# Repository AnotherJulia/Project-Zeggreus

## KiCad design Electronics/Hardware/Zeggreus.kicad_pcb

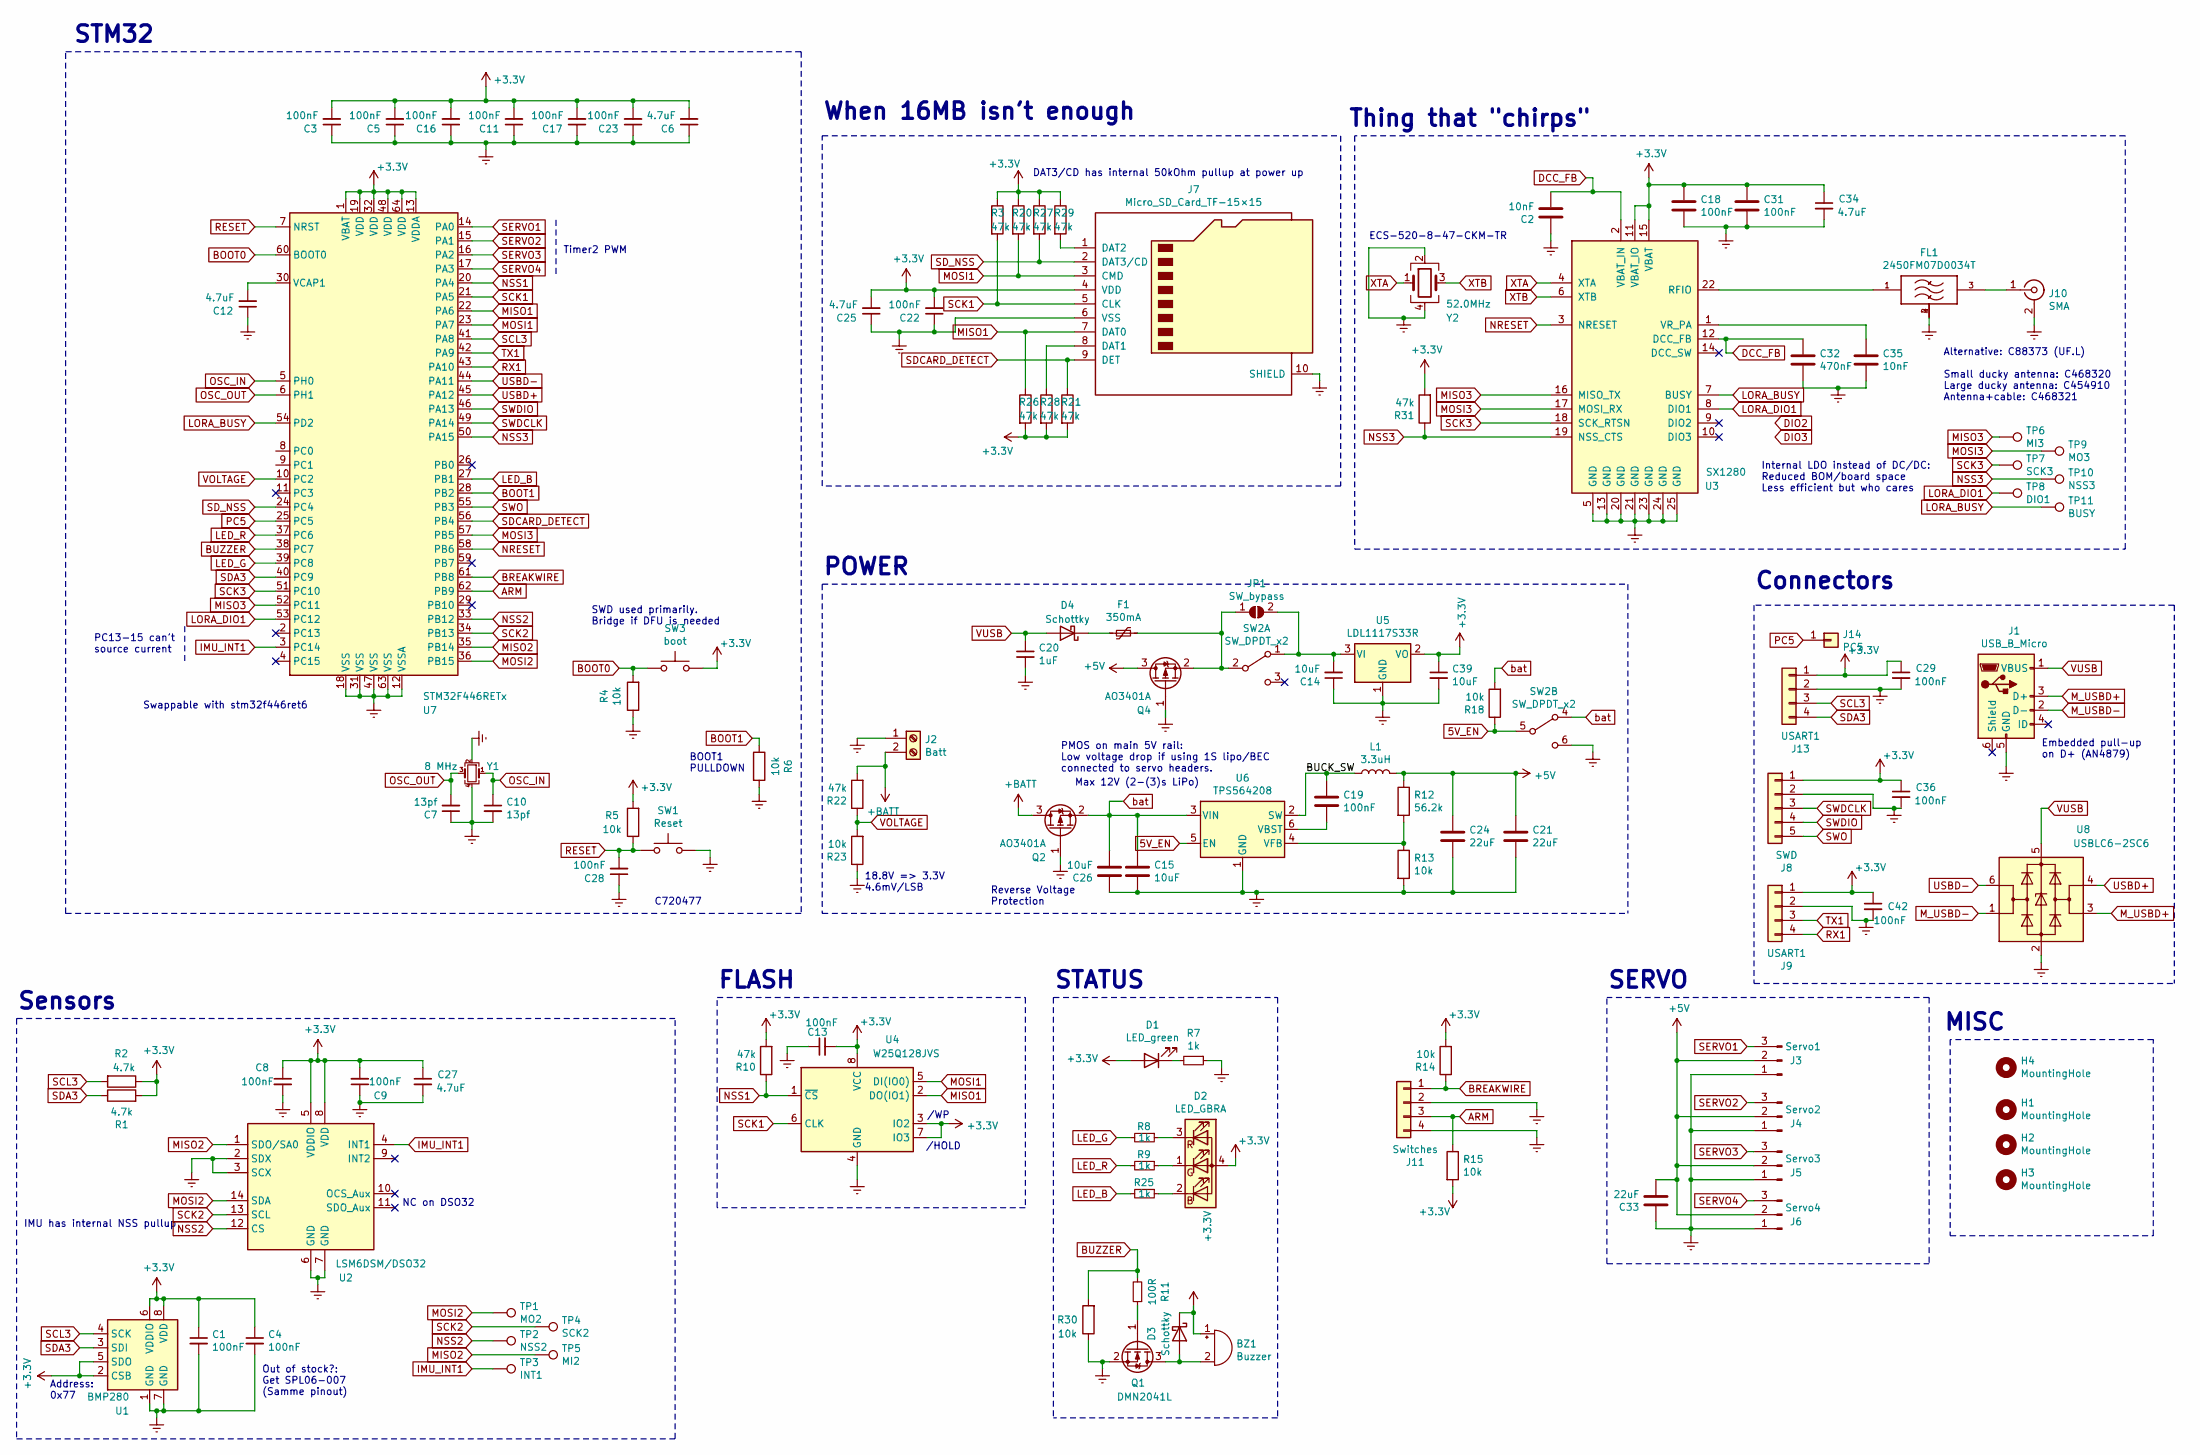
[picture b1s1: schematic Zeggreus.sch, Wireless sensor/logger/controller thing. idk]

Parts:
BZ1: Buzzer; 5x5mm_buzzer; LCSC C391030
C1, C3, C4, C5, C8, C9, C11, C13, C16, C17, C18, C19, C22, C23, C28, C29, C31, C36, C42: 100nF; C_0603_1608Metric; LCSC C45000
C2, C35: 10nF; C_0402_1005Metric; LCSC C77013
C6, C12, C25, C27, C34: 4.7uF; C_0603_1608Metric; LCSC C1705
C7, C10: 13pf; C_0603_1608Metric; LCSC C34243
C14, C15, C26, C39: 10uF; C_0805_2012Metric; LCSC C84416
C20: 1uF; C_0603_1608Metric; LCSC C26413
C21, C24, C33: 22uF; C_0805_2012Metric; LCSC C503482
C32: 470nF; C_0603_1608Metric; LCSC C106850
D1: LED_green; LED_0603_1608Metric; LCSC C205445
D2: LED_GBRA; LED_RGB_3.2X2.7mm; LCSC C375572
D3, D4: Schottky; D_SOD-123F; LCSC C353500
F1: 350mA; Fuse_1206_3216Metric; LCSC C269114
FL1: 2450FM07D0034T; FIL_2450FM07D0034T; PARTREV 1.2
H1, H2, H3, H4: MountingHole; MountingHole_3.2mm_M3
J1: USB_B_Micro; USB_Micro_B-Generic_SMT; LCSC C404968
J2: Batt; TerminalBlock_4Ucon_1x02_P3.50mm_Horizontal_blue; LCSC C474892
J3: Servo1; PinHeader_1x03_P2.54mm_Vertical
J4: Servo2; PinHeader_1x03_P2.54mm_Vertical
J5: Servo3; PinHeader_1x03_P2.54mm_Vertical
J6: Servo4; PinHeader_1x03_P2.54mm_Vertical
J7: Micro_SD_Card_TF-15×15; microSD_HC_TF-15x15; LCSC C111196
J8: SWD; PinHeader_1x05_P2.54mm_Vertical
J9, J13: USART1; PinHeader_1x04_P2.54mm_Vertical
J10: SMA; SMA_Molex_73251-2120_EdgeMount_Horizontal; LCSC C496550
J11: Switches; PinHeader_1x04_P2.54mm_Vertical
J14: PC5; PinHeader_1x01_P2.54mm_Vertical
JP1: SW_bypass; SolderJumper-2_P1.3mm_Open_RoundedPad1.0x1.5mm
L1: 3.3uH; L_5.4x5.2_H3; LCSC C429771
Q1: DMN2041L; SOT-23; LCSC C154903
Q2, Q4: AO3401A; SOT-23; LCSC C347476
R1, R2: 4.7k; R_0603_1608Metric; LCSC C116693
R3, R10, R20, R21, R22, R26, R27, R28, R29, R31: 47k; R_0603_1608Metric; LCSC C103657
R4, R5, R6, R13, R14, R15, R18, R23, R30: 10k; R_0603_1608Metric; LCSC C98220
R7, R8, R9, R25: 1k; R_0603_1608Metric; LCSC C14676
R11: 100R; R_0603_1608Metric; LCSC C163844
R12: 56.2k; R_0603_1608Metric; LCSC C168337
SW1: Reset; SW_Push_SPST_3×4×2; LCSC C720477
SW2: SW_DPDT_x2; SW_DPDT_MST22D18G2
SW3: boot; SW_Push_SPST_3×4×2; LCSC C720477
TP1: MO2; TestPoint_Pad_D1.0mm
TP2: NSS2; TestPoint_Pad_D1.0mm
TP3: INT1; TestPoint_Pad_D1.0mm
TP4: SCK2; TestPoint_Pad_D1.0mm
TP5: MI2; TestPoint_Pad_D1.0mm
TP6: MI3; TestPoint_Pad_D1.0mm
TP7: SCK3; TestPoint_Pad_D1.0mm
TP8: DIO1; TestPoint_Pad_D1.0mm
TP9: MO3; TestPoint_Pad_D1.0mm
TP10: NSS3; TestPoint_Pad_D1.0mm
TP11: BUSY; TestPoint_Pad_D1.0mm
U1: BMP280; Bosch_LGA-8_2x2.5mm_P0.65mm_ClockwisePinNumbering; LCSC C233787
U2: LSM6DSM/DSO32; Bosch_LGA-14_3x2.5mm_P0.5mm; LCSC C94048
U3: SX1280; QFN-24-1EP_4x4mm_P0.5mm_EP2.7x2.7mm_ThermalVias; LCSC C125969
U4: W25Q128JVS; SOIC-8_5.23x5.23mm_P1.27mm; LCSC C113767
U5: LDL1117S33R; SOT-223-3_TabPin2; LCSC C435835
U6: TPS564208; SOT-23-6; LCSC C486062
U7: STM32F446RETx; LQFP-64_10x10mm_P0.5mm; LCSC C69336
U8: USBLC6-2SC6; SOT-23-6; LCSC C558442
Y1: 8 MHz; Crystal_SMD_3225-4Pin_3.2x2.5mm; LCSC C400090
Y2: 52.0MHz; Oscillator_SMD_Abracon_ASCO-4Pin_1.6x1.2mm; LCSC C781784

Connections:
5V_EN: R18.1, SW2.5 (B), U6.5 (EN)
+3V3: BZ1.1 (-), C1.1, C3.2, C4.1, C5.2, C6.2, C8.1, C9.2, C11.2, C13.2, C16.2, C17.2, C18.1, C22.2, C23.2, C25.2, C27.1, C29.1, C31.1, C34.1, C36.1, C39.1, C42.1, D1.2 (A), D2.4 (A), D3.1 (K), J7.4 (VDD), J8.1, J9.1, J13.1, R1.2, R2.1, R3.1, R5.2, R10.2, R14.2, R15.2, R20.1, R21.2, R26.2, R27.1, R28.2, R29.1, R31.2, SW3.2, U1.2 (CSB), U1.5 (SDO), U1.6 (VDDIO), U1.8 (VDD), U2.5 (VDDIO), U2.8 (VDD), U3.11 (VBAT_IO), U3.15 (VBAT), U4.3 (IO2), U4.7 (IO3), U4.8 (VCC), U5.2 (VO), U7.1 (VBAT), U7.13 (VDDA), U7.19 (VDD), U7.32 (VDD), U7.48 (VDD), U7.64 (VDD)
+5V: C21.1, C24.1, C33.2, J3.2, J4.2, J5.2, J6.2, L1.2, Q4.3 (D), R12.1
+BATT: J2.2, Q2.3 (D), R22.2
/BUCK_SW: C19.2, L1.1, U6.2 (SW)
ARM: J11.3, R15.1, U7.62 (PB9)
BOOT0: R4.2, SW3.1, U7.60 (BOOT0)
BOOT1: R6.1, U7.28 (PB2)
BREAKWIRE: J11.1, R14.1, U7.61 (PB8)
BUZZER: R11.2, R30.2, U7.38 (PC7)
DCC_FB: C2.2, C32.1, U3.2 (VBAT_IN), U3.12 (DCC_FB)
Earth: C1.2, C2.1, C3.1, C4.2, C5.1, C6.1, C7.1, C8.2, C9.1, C10.2, C11.1, C12.1, C13.1, C14.1, C15.2, C16.1, C17.1, C18.2, C20.2, C21.2, C22.1, C23.1, C24.2, C25.1, C26.1, C27.2, C28.1, C29.2, C31.2, C32.2, C33.1, C34.2, C35.2, C36.2, C39.2, C42.2, FL1.2, FL1.4, J1.5 (GND), J2.1, J3.1, J4.1, J5.1, J6.1, J7.6 (VSS), J7.10 (SHIELD), J8.2, J9.2, J10.2 (Ext), J11.2, J11.4, J13.2, Q1.2 (S), Q2.1 (G), Q4.1 (G), R4.1, R6.2, R7.1, R13.2, R23.1, R30.1, SW1.2, SW2.6 (C), U1.1 (GND), U1.7 (GND), U2.2 (SDX), U2.3 (SCX), U2.6 (GND), U2.7 (GND), U3.5 (GND), U3.13 (GND), U3.20 (GND), U3.21 (GND), U3.23 (GND), U3.24 (GND), U3.25 (GND), U4.4 (GND), U5.1 (GND), U6.1 (GND), U7.12 (VSSA), U7.18 (VSS), U7.31 (VSS), U7.47 (VSS), U7.63 (VSS), U8.2 (GND), Y1.2, Y1.4, Y2.2, Y2.4
IMU_INT1: TP3.1, U2.4 (INT1), U7.3 (PC14)
LED_B: R25.2, U7.27 (PB1)
LED_G: R8.2, U7.39 (PC8)
LED_R: R9.2, U7.37 (PC6)
LORA_BUSY: TP11.1, U3.7 (BUSY), U7.54 (PD2)
LORA_DIO1: TP8.1, U3.8 (DIO1), U7.53 (PC12)
MISO1: J7.7 (DAT0), R26.1, U4.2 (DO(IO1)), U7.22 (PA6)
MISO2: TP5.1, U2.1 (SDO/SA0), U7.35 (PB14)
MISO3: TP6.1, U3.16 (MISO_TX), U7.52 (PC11)
MOSI1: J7.3 (CMD), R20.2, U4.5 (DI(IO0)), U7.23 (PA7)
MOSI2: TP1.1, U2.14 (SDA), U7.36 (PB15)
MOSI3: TP9.1, U3.17 (MOSI_RX), U7.57 (PB5)
M_USBD+: J1.3 (D+), U8.3 (I/O2)
M_USBD-: J1.2 (D-), U8.1 (I/O1)
NRESET: U3.3 (NRESET), U7.58 (PB6)
NSS1: R10.1, U4.1 (~CS), U7.20 (PA4)
NSS2: TP2.1, U2.12 (CS), U7.33 (PB12)
NSS3: R31.1, TP10.1, U3.19 (NSS_CTS), U7.50 (PA15)
unnamed: BZ1.2 (+), D3.2 (A), Q1.3 (D)
unnamed: C12.2, U7.30 (VCAP1)
unnamed: C14.2, JP1.2 (B), SW2.1 (A), U5.3 (VI)
unnamed: C19.1, U6.6 (VBST)
unnamed: C35.1, U3.1 (VR_PA)
unnamed: D1.1 (K), R7.2
unnamed: D2.1 (GK), R9.1
unnamed: D2.2 (BK), R25.1
unnamed: D2.3 (RK), R8.1
unnamed: D4.1 (K), F1.2
unnamed: F1.1, JP1.1 (A), Q4.2 (S), SW2.2 (B)
unnamed: FL1.1, U3.22 (RFIO)
unnamed: FL1.3, J10.1 (In)
unnamed: J7.1 (DAT2), R29.2
unnamed: J7.8 (DAT1), R28.1
unnamed: Q1.1 (G), R11.1
unnamed: R12.2, R13.1, U6.4 (VFB)
OSC_IN: C10.1, U7.5 (PH0), Y1.1
OSC_OUT: C7.2, U7.6 (PH1), Y1.3
PC5: J14.1, U7.25 (PC5)
RESET: C28.2, R5.1, SW1.1, U7.7 (NRST)
RX1: J9.4, U7.43 (PA10)
SCK1: J7.5 (CLK), R3.2, U4.6 (CLK), U7.21 (PA5)
SCK2: TP4.1, U2.13 (SCL), U7.34 (PB13)
SCK3: TP7.1, U3.18 (SCK_RTSN), U7.51 (PC10)
SCL3: J13.3, R2.2, U1.4 (SCK), U7.41 (PA8)
SDA3: J13.4, R1.1, U1.3 (SDI), U7.40 (PC9)
SDCARD_DETECT: J7.9 (DET), R21.1, U7.56 (PB4)
SD_NSS: J7.2 (DAT3/CD), R27.2, U7.24 (PC4)
SERVO1: J3.3, U7.14 (PA0)
SERVO2: J4.3, U7.15 (PA1)
SERVO3: J5.3, U7.16 (PA2)
SERVO4: J6.3, U7.17 (PA3)
SWDCLK: J8.3, U7.49 (PA14)
SWDIO: J8.4, U7.46 (PA13)
SWO: J8.5, U7.55 (PB3)
TX1: J9.3, U7.42 (PA9)
USBD+: U7.45 (PA12), U8.4 (I/O2)
USBD-: U7.44 (PA11), U8.6 (I/O1)
VOLTAGE: R22.1, R23.2, U7.10 (PC2)
VUSB: C20.1, D4.2 (A), J1.1 (VBUS), U8.5 (VBUS)
XTA: U3.4 (XTA), Y2.1
XTB: U3.6 (XTB), Y2.3
bat: C15.1, C26.2, Q2.2 (S), R18.2, SW2.4 (A), U6.3 (VIN)

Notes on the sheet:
/WP
/HOLD
Address: 0x77
BOOT1 PULLDOWN
STM32
FLASH
Sensors
STATUS
SERVO
POWER
MISC
Connectors
DAT3/CD has internal 50kOhm pullup at power up
IMU has internal NSS pullup
NC on DSO32
Embedded pull-up on D+ (AN4879)
Thing that "chirps"
Out of stock?: Get SPL06-007 (Samme pinout)
PMOS on main 5V rail: Low voltage drop if using 1S lipo/BEC connected to servo headers.
Timer2 PWM
PC13-15 can't source current
18.8V => 3.3V 4.6mV/LSB
Internal LDO instead of DC/DC: Reduced BOM/board space Less efficient but who cares
SWD used primarily. Bridge if DFU is needed
When 16MB isn't enough
C720477
Alternative: C88373 (UF.L) Small ducky antenna: C468320 Large ducky antenna: C454910 Antenna+cable: C468321
Swappable with stm32f446ret6
ECS-520-8-47-CKM-TR
Max 12V (2-(3)s LiPo)
Reverse Voltage Protection

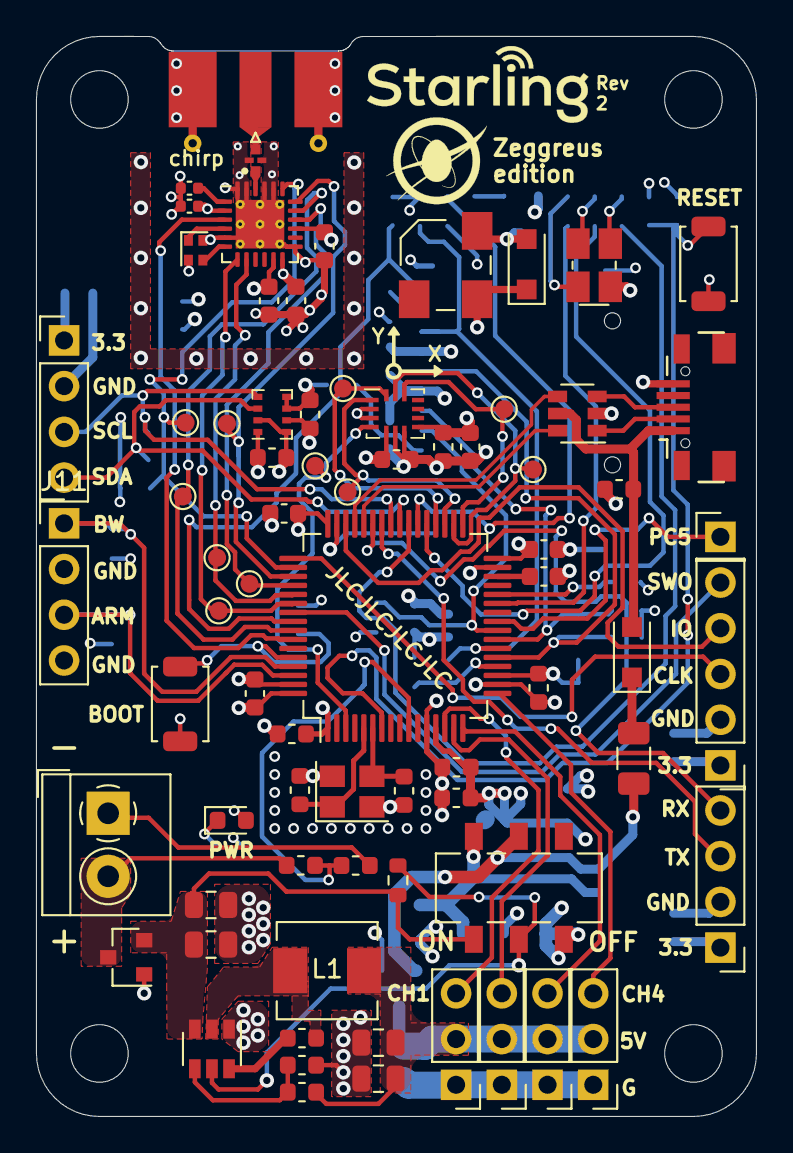
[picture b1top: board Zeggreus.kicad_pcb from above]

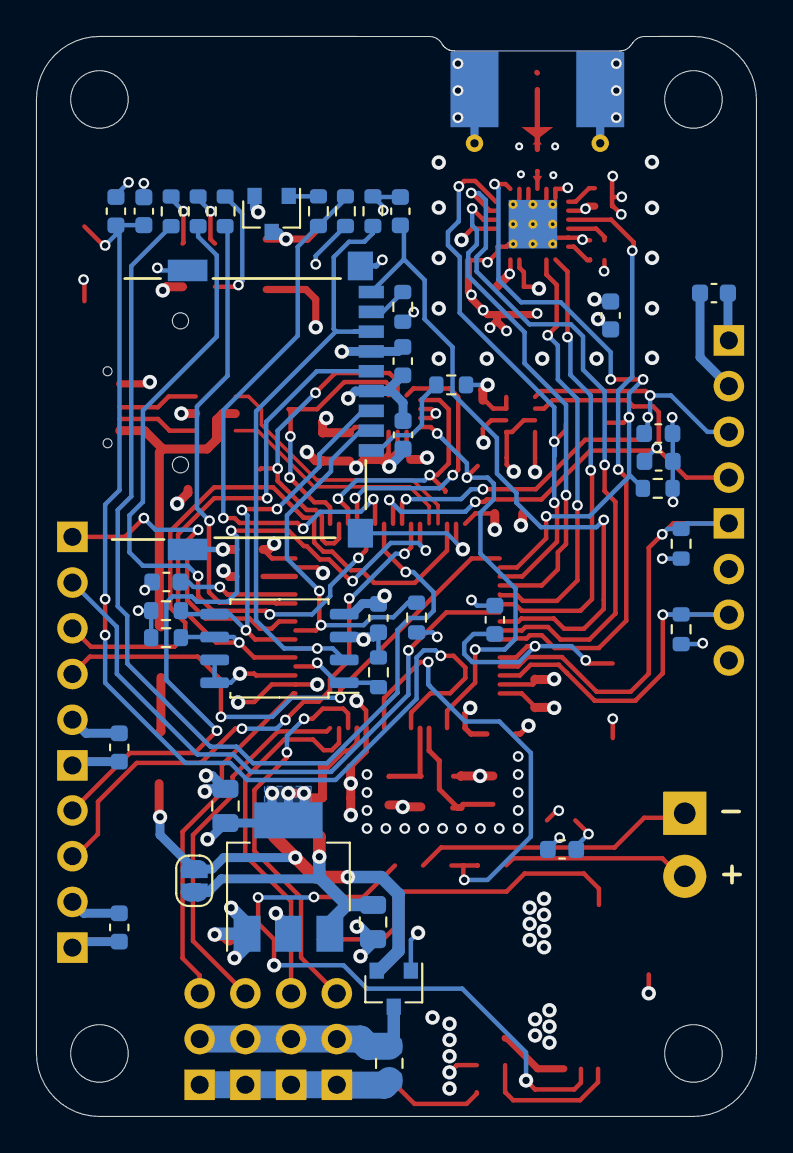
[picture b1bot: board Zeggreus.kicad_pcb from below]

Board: 4 copper layers, 40.0 x 60.0 mm, 117 parts (39 on the bottom side), 74 nets.

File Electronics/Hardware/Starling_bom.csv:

"Id";"Designator";"Package";"Quantity";"Designation";"Supplier and ref";
1;"J2";"TerminalBlock_4Ucon_1x02_P3.50mm_Horizontal_blue";1;"Batt";;;
2;"J11";"TerminalBlock_4Ucon_1x02_P3.50mm_Horizontal_blue";1;"P1";;;
3;"J12";"TerminalBlock_4Ucon_1x02_P3.50mm_Horizontal_blue";1;"P2";;;
4;"G***";"logo";1;"LOGO";;;
5;"TP11";"TestPoint_Pad_D1.0mm";1;"BUSY";;;
6;"TP10";"TestPoint_Pad_D1.0mm";1;"NSS3";;;
7;"TP9";"TestPoint_Pad_D1.0mm";1;"MO3";;;
8;"TP8";"TestPoint_Pad_D1.0mm";1;"DIO1";;;
9;"TP7";"TestPoint_Pad_D1.0mm";1;"SCK3";;;
10;"TP6";"TestPoint_Pad_D1.0mm";1;"MI3";;;
11;"TP5";"TestPoint_Pad_D1.0mm";1;"MI2";;;
12;"TP4";"TestPoint_Pad_D1.0mm";1;"SCK2";;;
13;"TP3";"TestPoint_Pad_D1.0mm";1;"INT1";;;
14;"TP2";"TestPoint_Pad_D1.0mm";1;"NSS2";;;
15;"TP1";"TestPoint_Pad_D1.0mm";1;"MO2";;;
16;"R32,R19,R11";"R_0603_1608Metric";3;"100R";;;
17;"J14";"PinHeader_1x01_P2.54mm_Vertical";1;"PC5";;;
18;"C29,C28,C23,C17,C16,C22,C9,C8,C4,C13,C1,C3,C42,C19,C36,C5,C11";"C_0603_1608Metric";17;"100nf";;;
19;"C27,C34,C25,C12,C6";"C_0603_1608Metric";5;"4.7uF";;;
20;"SW3";"SW_DPDT_MST22D18G2";1;"SW_DPDT_x2";;;
21;"SW1";"SW_Push_SPST_3×4×2";1;"Reset";;;
22;"J10";"SMA_Molex_73251-2120_EdgeMount_Horizontal";1;"SMA";;;
23;"JP1";"SolderJumper-2_P1.3mm_Open_RoundedPad1.0x1.5mm";1;"BOOT1";;;
24;"J13,J9";"PinHeader_1x04_P2.54mm_Vertical";2;"USART1";;;
25;"U8";"SOT-23-6";1;"USBLC6-2SC6";;;
26;"R31,R29,R28,R27,R26,R20,R3,R10,R21,R16,R14,R22";"R_0603_1608Metric";12;"47k";;;
27;"R30,R17,R15,R23,R6,R5,R4,R13";"R_0603_1608Metric";8;"10k";;;
28;"Q4";"SOT-23";1;"AO3401A";;;
29;"C14,C15,C39,C26";"C_0805_2012Metric";4;"10uF";;;
30;"Y2";"Crystal_SMD_2016-4Pin_2.0x1.6mm";1;"52.0MHz";;;
31;"FL1";"FIL_2450FM07D0034T";1;"2450FM07D0034T";;;
32;"R24,R18,R25,R9,R8,R7";"R_0603_1608Metric";6;"1k";;;
33;"U3";"QFN-24-1EP_4x4mm_P0.5mm_EP2.7x2.7mm_ThermalVias";1;"SX1280";;;
34;"C35,C2";"C_0402_1005Metric";2;"10nF";;;
35;"C32";"C_0603_1608Metric";1;"470nF";;;
36;"C31,C18";"C_0603_1608Metric";2;"100nF";;;
37;"J8";"PinHeader_1x05_P2.54mm_Vertical";1;"SWD";;;
38;"J1";"USB_Micro_B-Generic_SMT";1;"USB_B_Micro";;;
39;"L1";"L_5.4x5.2_H3";1;"3.3uH";;;
40;"H4,H3,H2,H1";"MountingHole_3.2mm_M3";4;"MountingHole";;;
41;"D2";"LED_RGB_3.2X2.7mm";1;"LED_GBRA";;;
42;"BZ1";"5x5mm_buzzer";1;"Buzzer";;;
43;"C24,C21,C33";"C_0805_2012Metric";3;"22uF";;;
44;"D4";"D_SOD-123F";1;"Schottky";;;
45;"Q1,Q3,Q2";"SOT-23";3;"DMN2041L";;;
46;"F1";"Fuse_1206_3216Metric";1;"350mA";;;
47;"J7";"microSD_HC_TF-15x15";1;"Micro_SD_Card_TF-15×15";;;
48;"U2";"Bosch_LGA-14_3x2.5mm_P0.5mm";1;"LSM6DSM/DSO32";;;
49;"U7";"LQFP-64_10x10mm_P0.5mm";1;"STM32F411RETx";;;
50;"U4";"SOIC-8_5.23x5.23mm_P1.27mm";1;"W25Q128JVS";;;
51;"U6";"SOT-23-6";1;"TPS564208";;;
52;"D1";"LED_0603_1608Metric";1;"LED_green";;;
53;"Y1";"Crystal_SMD_3225-4Pin_3.2x2.5mm";1;"8 MHz";;;
54;"U5";"SOT-223-3_TabPin2";1;"LDL1117S33R";;;
55;"J3";"PinHeader_1x03_P2.54mm_Vertical";1;"Servo1";;;
56;"J4";"PinHeader_1x03_P2.54mm_Vertical";1;"Servo2";;;
57;"J5";"PinHeader_1x03_P2.54mm_Vertical";1;"Servo3";;;
58;"U1";"Bosch_LGA-8_2x2.5mm_P0.65mm_ClockwisePinNumbering";1;"BMP280";;;
59;"J6";"PinHeader_1x03_P2.54mm_Vertical";1;"Servo4";;;
60;"C20";"C_0603_1608Metric";1;"1uF";;;
61;"C10,C7";"C_0603_1608Metric";2;"13pf";;;
62;"R12";"R_0603_1608Metric";1;"56.2k";;;
63;"R2,R1";"R_0603_1608Metric";2;"4.7k";;;

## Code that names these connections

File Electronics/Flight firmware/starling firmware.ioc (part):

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Mcu.Name=STM32F446R(C-E)Tx
Mcu.Package=LQFP64
Mcu.UserName=STM32F446RETx
PA0-WKUP.GPIOParameters=GPIO_PuPd,GPIO_Label
PA0-WKUP.GPIO_Label=RBF
PA0-WKUP.GPIO_PuPd=GPIO_PULLUP
PA0-WKUP.Signal=GPIO_Input
PA1.Signal=S_TIM2_CH2
PA10.GPIOParameters=GPIO_PuPd,GPIO_Label
PA10.GPIO_Label=EXPORT_BLACKBOX
PA10.GPIO_PuPd=GPIO_PULLUP
PA10.Signal=GPIO_Input
PA11.Mode=Device_Only
PA11.Signal=USB_OTG_FS_DM
PA12.Mode=Device_Only
PA12.Signal=USB_OTG_FS_DP
PA13.Mode=Trace_Asynchronous_SW
PA13.Signal=SYS_JTMS-SWDIO
PA14.Mode=Trace_Asynchronous_SW
PA14.Signal=SYS_JTCK-SWCLK
PA15.GPIOParameters=GPIO_Label
PA15.GPIO_Label=LORA_NSS
PA15.Signal=GPIO_Output
PA2.GPIOParameters=GPIO_Label
PA2.GPIO_Label=CAM_POWER
PA2.Signal=GPIO_Output
PA3.Signal=S_TIM2_CH4
PA4.GPIOParameters=GPIO_Label
PA4.GPIO_Label=FLASH_NSS
PA4.Signal=GPIO_Output
PA5.Mode=Full_Duplex_Master
PA5.Signal=SPI1_SCK
PA6.Mode=Full_Duplex_Master
PA6.Signal=SPI1_MISO
PA7.Mode=Full_Duplex_Master
PA7.Signal=SPI1_MOSI
PA8.Mode=I2C
PA8.Signal=I2C3_SCL
PB1.Signal=S_TIM3_CH4
PB12.GPIOParameters=GPIO_Label
PB12.GPIO_Label=SPI2_NSS
PB12.Signal=GPIO_Output
PB13.Mode=Full_Duplex_Master
PB13.Signal=SPI2_SCK
PB14.Mode=Full_Duplex_Master
PB14.Signal=SPI2_MISO
PB15.Mode=Full_Duplex_Master
PB15.Signal=SPI2_MOSI
PB3.Mode=Trace_Asynchronous_SW
PB3.Signal=SYS_JTDO-SWO
PB4.GPIOParameters=GPIO_Label
PB4.GPIO_Label=SD_DETECT
PB4.Signal=GPIO_Input
PB5.Mode=Full_Duplex_Master
PB5.Signal=SPI3_MOSI
PB6.GPIOParameters=PinState,GPIO_Label
PB6.GPIO_Label=LORA_RESET
PB6.PinState=GPIO_PIN_SET
PB6.Signal=GPIO_Output
PB8.GPIOParameters=GPIO_PuPd,GPIO_Label
PB8.GPIO_Label=BREAKWIRE
PB8.GPIO_PuPd=GPIO_PULLUP
PB8.Signal=GPIO_Input
PB9.GPIOParameters=GPIO_PuPd,GPIO_Label
PB9.GPIO_Label=ARM
PB9.GPIO_PuPd=GPIO_PULLUP
PB9.Signal=GPIO_Input
PC10.Mode=Full_Duplex_Master
PC10.Signal=SPI3_SCK
PC11.Mode=Full_Duplex_Master
PC11.Signal=SPI3_MISO
PC12.GPIOParameters=GPIO_Label
PC12.GPIO_Label=LORA_DIO1
PC12.Signal=GPIO_Input
PC14-OSC32_IN.GPIOParameters=GPIO_Label
PC14-OSC32_IN.GPIO_Label=IMU_INT
PC14-OSC32_IN.Signal=GPXTI14
PC2.GPIOParameters=GPIO_Label
PC2.GPIO_Label=VOLTAGE
PC2.Signal=ADCx_IN12
PC4.GPIOParameters=GPIO_Label
PC4.GPIO_Label=SD_NSS
PC4.Signal=GPIO_Output
PC5.GPIOParameters=GPIO_PuPd,GPIO_Label
PC5.GPIO_Label=VTX_BTN1
PC5.GPIO_PuPd=GPIO_PULLDOWN
PC5.Signal=GPIO_Output
PC6.Signal=S_TIM3_CH1
PC7.Signal=S_TIM3_CH2
PC8.Signal=S_TIM3_CH3
PC9.Mode=I2C
PC9.Signal=I2C3_SDA
PD2.GPIOParameters=GPIO_Label
PD2.GPIO_Label=LORA_BUSY
PD2.Signal=GPIO_Input
PH0-OSC_IN.Mode=HSE-External-Oscillator
PH0-OSC_IN.Signal=RCC_OSC_IN
PH1-OSC_OUT.Mode=HSE-External-Oscillator
PH1-OSC_OUT.Signal=RCC_OSC_OUT
RCC.HSE_VALUE=8000000
RCC.SYSCLKFreq_VALUE=180000000
RCC.SYSCLKSource=RCC_SYSCLKSOURCE_PLLCLK
board=custom

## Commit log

2021-02-20 Initializing Folders
2021-02-20 Added Untitled Diagram.drawio
2021-02-20 Create untiteled rocket 4.ork
    a simulation of the rocket
2021-02-20 CAD creation
    First instance of the CAD document
2021-02-20 Refining
    general refinement of all sub-assemblies,
    static simulation of the fin bending
2021-02-21 Added electronics hardware files
2021-02-21 Update schematic
2021-02-21 preliminary design
    bolt holes, stringers, bulkheads, nosecone done
2021-02-21 detailing 1
    weight optimised, simulations added, further detailing of the rocket design
2021-02-21 forward swept fins
    Fins for "Fleggx" configuration adjusted
2021-02-21 Materials updated, Coupling creation
    Bulkhead materials changed from alu to plastic for weight optimisation
    Coupling collar preliminary design created
2021-02-23 coupling mechanism refinements
    overlapping parts designed, second part added
2021-02-23 electronics support
    Added t-mount for electronics and modified top bulkhead to support it.
2021-02-24 Added mission patch files and made minor changes to B-210
2021-02-24 Added PCB 3d model
2021-02-24 Started working on 3D printed parts for Yagi antenna
2021-02-25 (Almost) complete yagi antenna design
2021-02-25 Added electronics to rocket model
2021-02-25 added ground station PCB
2021-02-26 Worked on Yagi antenna design
2021-02-27 capsule base created
    minor adjustments
2021-02-27 Minor changes to Yagi design
2021-02-27 mission patch added
2021-02-27 Antenna model and PCB tweaks
2021-02-27 PR folder initiation
2021-02-28 3d print folder initiation
2021-02-28 nose cone change
2021-02-28 Modifed servo model
2021-02-28 Added servo horn
2021-02-28 decoupling refinements
2021-02-28 (Even more) minor changes to Yagi design
2021-02-28 pre-rendering
2021-02-28 Worked on egg capsule
2021-02-28 general changes
2021-03-02 Updated Renderings
    - Fins
    - Coupling Servo
2021-03-05 More changes to egg capsule
2021-03-05 Worked on egg capsule design
    - threaded lid dimensions have to be modified to make everything fit properly
2021-03-09 Changed egg capsule lid design
    - Now requires 4 M3 screws and 4 M3 threaded inserts
2021-03-15 Adjusted egg capsule lid dimensions
2021-03-17 update electronics and added camera model
2021-03-20 Put chamfers to make the parts look more professional (also changed some dimensions)
2021-03-23 Made yagi boom drawing
2021-03-23 Minor changes to lid dimensions
2021-03-28 Added camera to assembly
2021-03-28 parachute sizing
    paragore sizing
2021-04-01 alu bulkhead
    new bulkhead design for increased strength and decreased weight
2021-04-01 Nosecone update
    - Added nosecone attachment system
    - Structural enhancements to the nosecone
2021-04-01 Re-added changes
2021-04-01 fin asssembly D-1100 added
    new assembly with with bends and rivet holes
2021-04-01 Nose cone updates
2021-04-02 Update electronics mount
2021-04-06 Changed Yagi mount size
2021-04-10 parachute design
2021-04-11 Changes to Yagi elements
2021-04-12 Virtual camera and tweaked constraints
2021-04-13 Added core flight firmware
2021-04-18 Added receiver PCB
2021-04-18 Created yagi stock
2021-04-19 Basic telemetry working
2021-04-20 Updated decoupling system
2021-04-21 Added screw holes to EPC bulkhead and top stringers
2021-04-21 Refreshed project files
2021-04-21 Added servo mounting holes and wiring routes for servo stuff and things and more things and stuff ya know lol
2021-04-21 Adjusted parachute guide holes
2021-04-22 lunch lugs added
2021-04-22 realignment of the launch lugs
2021-04-22 Tweaks to skin, sep mechanism and lugs
2021-04-24 Tweak seperation mechanism
2021-04-24 Basic working RTOS
2021-04-25 Cant remember what I did but its probably important so im pushing the changes
2021-04-25 Revert "Cant remember what I did but its probably important so im pushing the changes"
    This reverts commit e249268626986ff6a741a6366d0b49020ceb1070.
2021-04-25 Update clamp band tolerances
2021-04-25 Clamp band alignment notch
2021-04-25 Tweak sep mechanism
2021-04-26 Clamp band tweaks
2021-04-28 Tweaked sep mechanism
2021-04-29 Tweak clamp band
2021-04-29 Split up Yagi for printing
2021-05-01 Update camera model
2021-05-02 Add base ground station firmware
2021-05-02 Made modifications to stock and bulkhead
2021-05-02 Tweaked bulkhead size
2021-05-02 firmware tweaks
2021-05-02 SCD
    - Added LoraTarget print
    - Haven't tested with the sending thingy yet
2021-05-03 fins and laser cut
2021-05-03 Added hole to engine bulkhead
2021-05-04 Expand clamp band
2021-05-04 refinements, fins, lasercutting
2021-05-04 hybrid bulkhead
2021-05-04 Modified bulkheads
2021-05-04 Minor modifications to nosecone
2021-05-04 Refractor telemetry code
2021-05-06 fins
2021-05-06 Created 3D printed part of fin
2021-05-06 lasercut
2021-05-07 Fixed some stuff?
2021-05-07 Revert bulkhead changes
2021-05-07 Add cutout to clamp bands
2021-05-08 Update some files
2021-05-08 paragore change
2021-05-08 Add video transmitter mount
2021-05-08 Idek tbh
2021-05-09 Adjusted bulkhead sizes
2021-05-10 Fix merge conflicts
2021-05-10 Firmware update
2021-05-11 Created yagi electronics mount
2021-05-12 added telemetry package struct
2021-05-13 Tweak engine alignment bulkhead thing
2021-05-15 Toggle onboard recording
2021-05-15 Yagi electronics mount
2021-05-15 Added Serial Studio .json
    - Can be found under Electronics :100:
2021-05-18 Added helical antenna reflector
2021-05-18 Create script to present time in OBS
2021-05-18 Add helical antenna reflector drawing
2021-05-18 UPDATED YAGI ELECTRONICS MOUNT AYAYAYAYAYAYAYAYYAYAYAYAYAYAYAAAAAAAAAAAAAAAAAAAAAAAAAAAAAAAAAAAAAAAAAAAAAAAAAAAAAAAA
2021-05-18 NOW YOU CAN PRINT IT AAAAAAAAAAAAAAAAAAAAAAAAAAAAAAAAAAAAAAAAAAAAAAAAAAAAAAAAAAAAAAAAAAAAAAAAAAAAAAAAAAAA
2021-05-19 Implement sensor DMA to speed things up
2021-05-21 Add engine alignment cone
2021-05-21 Added engine alignment cone to model
2021-05-25 Antenna simulations
2021-05-27 Add data logging
2021-05-29 added flight data
